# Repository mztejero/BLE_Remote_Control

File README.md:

This remote control is designed to send incremental inputs over Bluetooth Low Energy. In this specific application, steering and throttle values are set with the rotary encoders and the x and y values of the joysticks are set in a range of -100 to 100. All of these values are sent as a package over BLE.
Running the ```ble_test.py``` shows the unpacked messages being received as shown below. 

# ESP-IDF
The file architecture is split into each of the remote's functions with each ```.c``` file also havng a complementary ```.h``` file allowing variable and function sharng across the project.
The files can be found in ```BLE_Remote_Control/main```:
```
config.c
joystick.c
bluetooth.c
encoder.c
lcd.c
buttons.c
main.c
```
```config.c```      Sets up and names the GPIO's used on the ESP32. <br>
```joystick.c```    Reads ADC values from the joystick potentiometers, estimates offsets, and converts the values into a range from -100 to 100. <br>
```bluetooth.c```  Uses NimBLE to run the ESP32 as a server by advertising through a GAP and publishing data packets through a GATT at 50 Hz. <br>
```encoder.c```     Sets up interrupts on quadrature encoders A and B terminals with tasks for counting which are added to queues. <br>
```lcd.c ```        Handles communication with LCD 16x02 via I<sup>2</sup>C. Transfers data through 4-bit nibbles and prints values on the screen (as shown in first picture). <br>
```buttons.c```     Placeholder script for reading switch values from encoders and joysticks. These are not currently used in this project. <br>
```main.c```        Main script for initializing and running the project on ESP32.

# Schematics

This PCB is designed using the following components:

## SMD Components
ESP32-WROOM-32E -- Microcontroller used to run firmware, read sensors, write to actuators, and handle BLE communication. <br>
CP2102A USB-to-UART -- Interface for uploading code to the ESP32-WROOM-32E. The NPN transistors circuitry automatically put the ESP32 into bootloader mode when a new upload happens.<br>
<br>
PCF8574A I2C I/O for LCD communication -- Uses SCL and SDA to convert I<sup>2</sup>C data into bits to send to the LCD 16x02. Circuitry implements n-type MOSFETs for level shifting between 5V and 3V3 <br>
AMS1117-3.3 -- Converts 5V into 3.3V for components requiring 3V3<br>

## Hand-Soldered Components
Rotary Encoders -- Quadrature encoders with A and B terminals connected to GPIOs with pull-ups. Interrupts on these pull-ups are triggered upon rotation. <br>
Joysticks -- Use 2 potentiometers, one for x direction and one for y direction. These values are read through the ESP32's ADC. <br>
LCD 16x02 -- Displays characters on a 16×2 grid from data bits. <br>
Potentiometer -- Adjusts LCD lighting. <br>

# Final PCB Design

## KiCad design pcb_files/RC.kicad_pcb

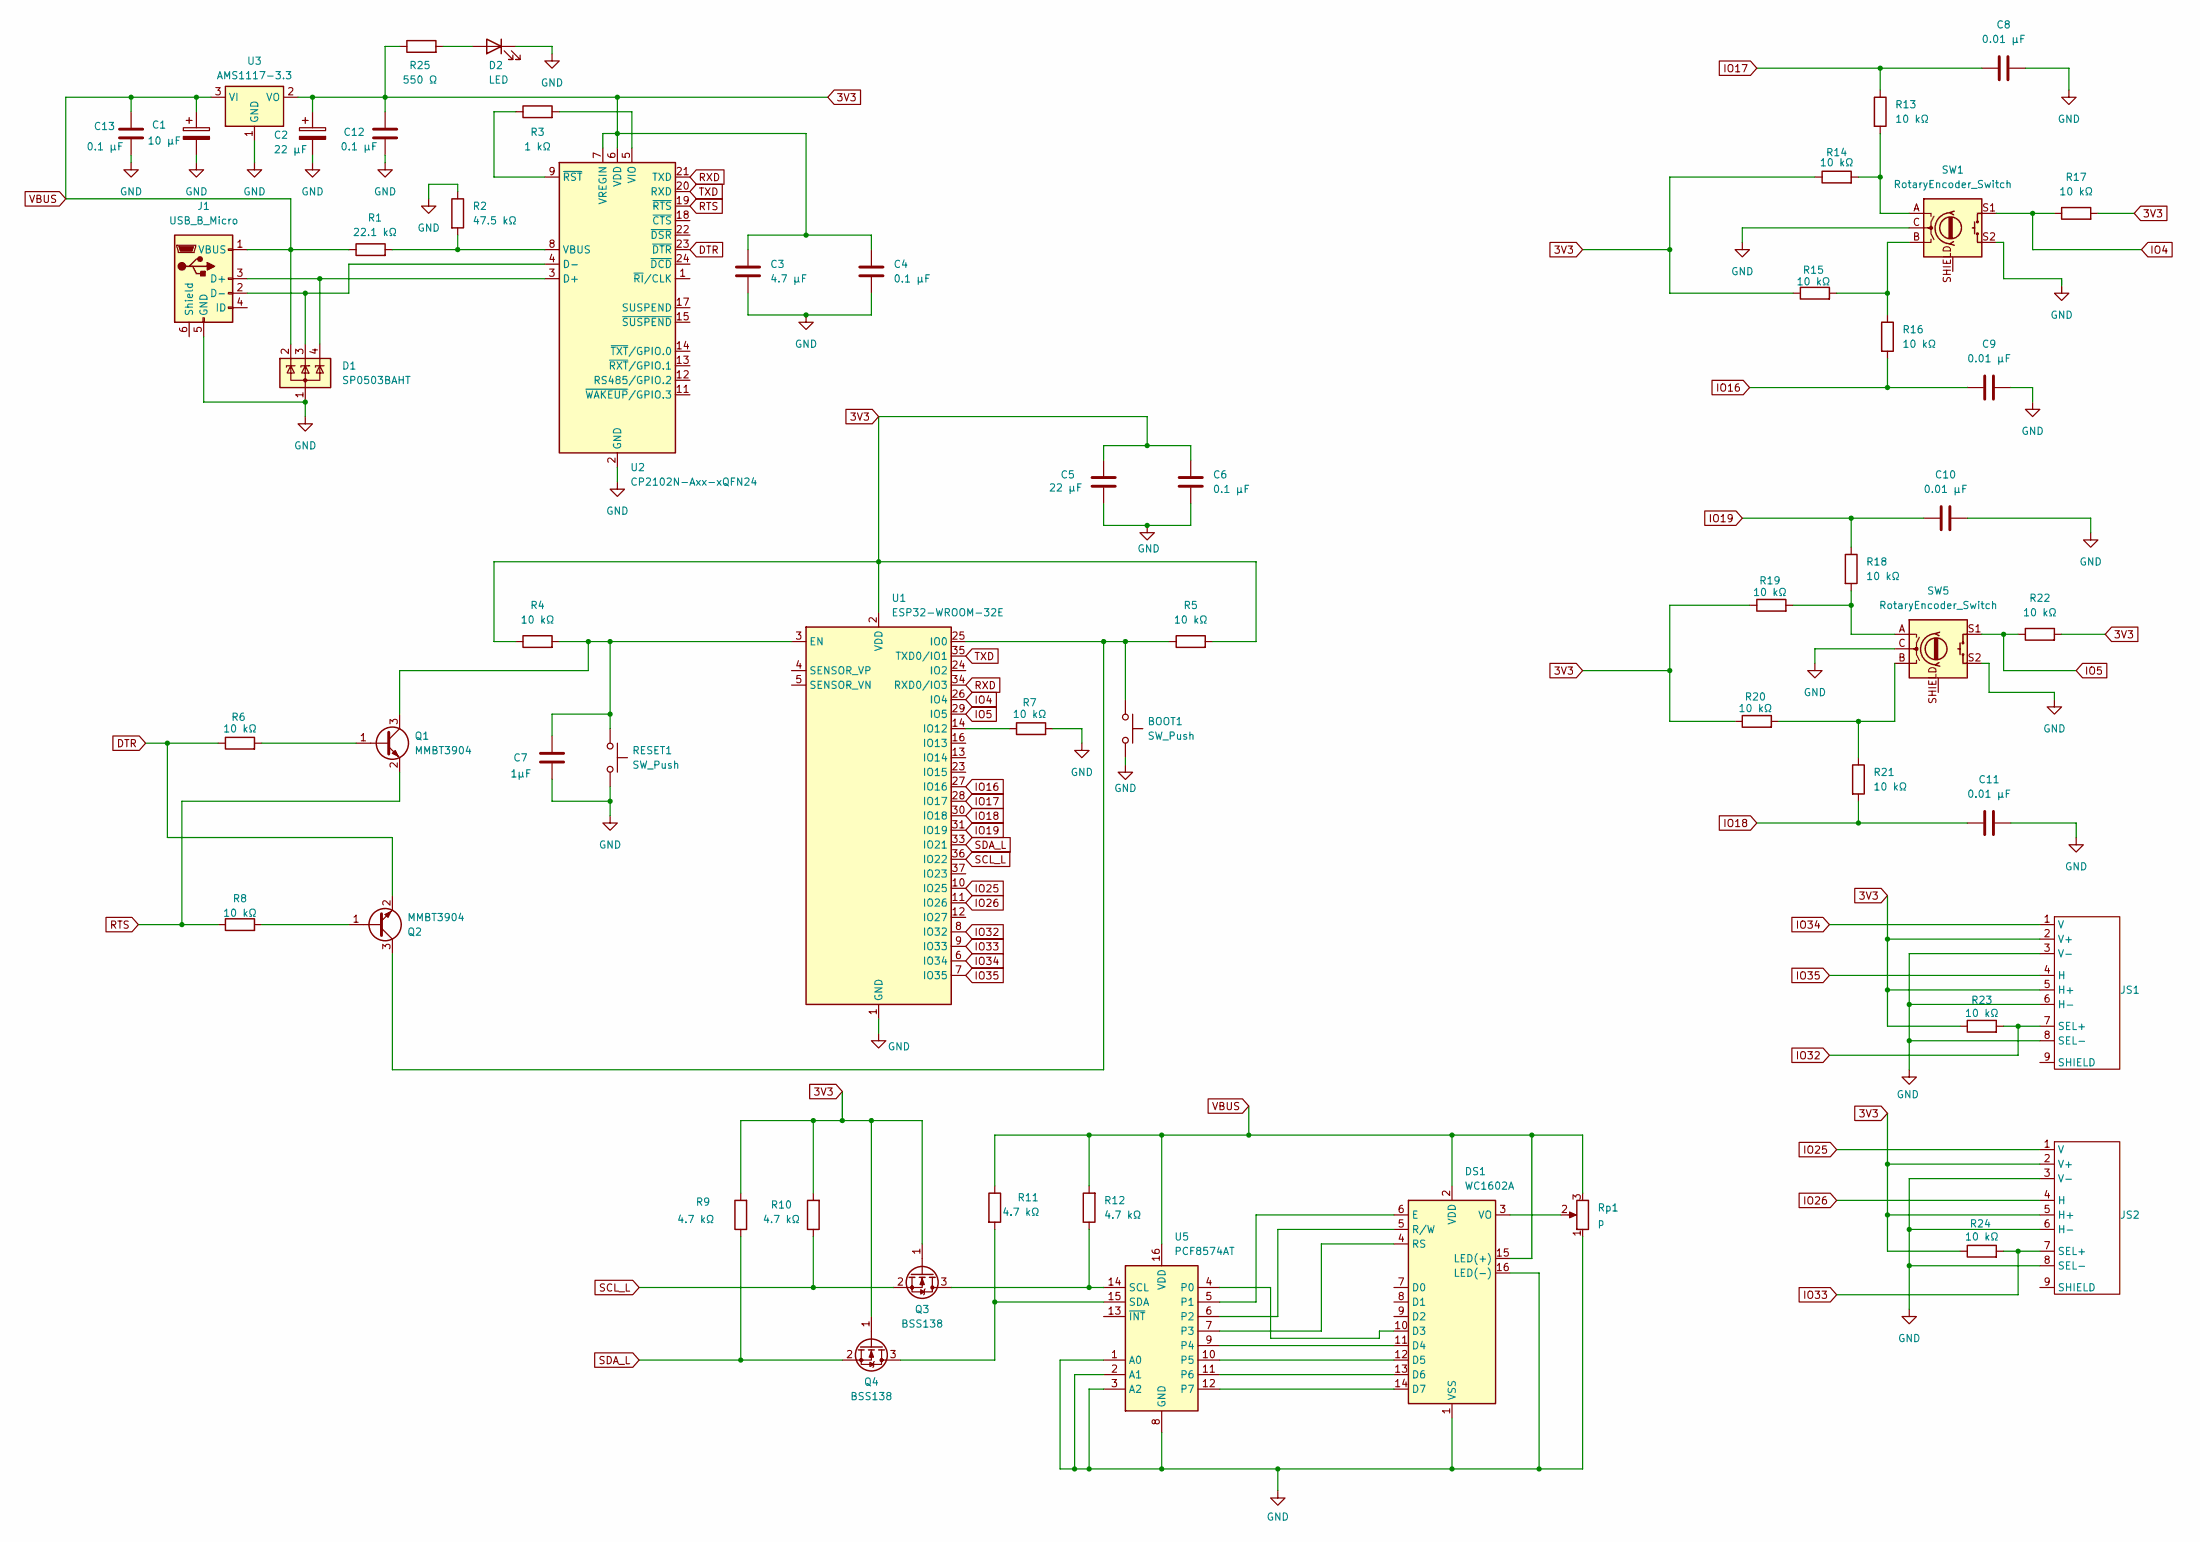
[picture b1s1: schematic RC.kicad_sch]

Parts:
BOOT1: SW_Push; SW_SPST_PTS647_Sx38
C1: 10 µF; CP_EIA-2012-12_Kemet-R
C2: 22 µF; CP_EIA-2012-12_Kemet-R
C3: 4.7 µF; C_0805_2012Metric
C4, C6, C12, C13: 0.1 µF; C_0603_1608Metric
C5: 22 µF; C_0805_2012Metric
C7: 1µF; C_0805_2012Metric
C8, C9, C10, C11: 0.01 µF; C_0603_1608Metric
D1: SP0503BAHT; SOT-143
D2: LED; LED_0603_1608Metric
DS1: WC1602A
J1: USB_B_Micro; USB_Micro-B_Amphenol_10103594-0001LF_Horizontal
JS1, JS2: Joystick
Q1, Q2: MMBT3904; SOT-23
Q3, Q4: BSS138; SOT-23
R1: 22.1 kΩ; R_0805_2012Metric
R2: 47.5 kΩ; R_0603_1608Metric
R3: 1 kΩ; R_0603_1608Metric
R4, R5, R6, R7, R8, R13, R14, R15, R16, R17, R18, R19, R20, R21, R22, R23, R24: 10 kΩ; R_0603_1608Metric
R9, R10, R11, R12: 4.7 kΩ; R_0603_1608Metric
R25: 550 Ω; R_0603_1608Metric
RESET1: SW_Push; SW_SPST_PTS647_Sx38
Rp1: p; Potentiometer_Bourns_3386P_Vertical
SW1, SW5: RotaryEncoder_Switch; Rotary_Encoder_RC
U1: ESP32-WROOM-32E
U2: CP2102N-Axx-xQFN24; QFN-24-1EP_4x4mm_P0.5mm_EP2.6x2.6mm
U3: AMS1117-3.3; SOT-223-3_TabPin2
U5: PCF8574AT; SOIC-16W_7.5x10.3mm_P1.27mm

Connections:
3V3: C2.1, C3.1, C4.1, C5.1, C6.1, C12.1, JS1.2 (V+), JS1.5 (H+), JS2.2 (V+), JS2.5 (H+), Q3.1 (G), Q4.1 (G), R4.1, R5.2, R9.2, R10.2, R14.1, R15.1, R17.2, R19.1, R20.1, R22.2, R23.1, R24.1, R25.1, U1.2 (VDD), U2.6 (VDD), U2.7 (VREGIN), U3.2 (VO)
DTR: Q2.2 (E), R6.1, U2.23 (~DTR)
GND: BOOT1.2, C1.2, C2.2, C3.2, C4.2, C5.2, C6.2, C7.2, C8.2, C9.2, C10.2, C11.2, C12.2, C13.2, D1.1 (A), D2.1 (K), DS1.1 (VSS), DS1.16 (LED(-)), J1.5 (GND), JS1.3 (V-), JS1.6 (H-), JS1.8 (SEL-), JS2.3 (V-), JS2.6 (H-), JS2.8 (SEL-), R2.1, R7.2, RESET1.2, Rp1.1, SW1.C, SW1.S2, SW5.C, SW5.S2, U1.1 (GND), U1.15 (GND), U1.38 (GND), U1.39 (GND), U2.2 (GND), U2.25 (GND), U3.1 (GND), U5.1 (A0), U5.2 (A1), U5.3 (A2), U5.8 (GND)
IO4: R17.1, SW1.S1, U1.26 (IO4)
IO5: R22.1, SW5.S1, U1.29 (IO5)
IO16: C9.1, R16.2, U1.27 (IO16)
IO17: C8.1, R13.1, U1.28 (IO17)
IO18: C11.1, R21.2, U1.30 (IO18)
IO19: C10.1, R18.1, U1.31 (IO19)
IO25: JS2.1 (V), U1.10 (IO25)
IO26: JS2.4 (H), U1.11 (IO26)
IO32: JS1.7 (SEL+), R23.2, U1.8 (IO32)
IO33: JS2.7 (SEL+), R24.2, U1.9 (IO33)
IO34: JS1.1 (V), U1.6 (IO34)
IO35: JS1.4 (H), U1.7 (IO35)
unnamed: D2.2 (A), R25.2
unnamed: DS1.10 (D3), U5.4 (P0)
unnamed: DS1.11 (D4), U5.9 (P4)
unnamed: DS1.12 (D5), U5.10 (P5)
unnamed: DS1.13 (D6), U5.11 (P6)
unnamed: DS1.14 (D7), U5.12 (P7)
unnamed: DS1.6 (E), U5.5 (P1)
unnamed: DS1.4 (RS), U5.7 (P3)
unnamed: DS1.5 (R/W), U5.6 (P2)
unnamed: DS1.3 (VO), Rp1.2
unnamed: D1.4 (K), J1.3 (D+), U2.3 (D+)
unnamed: D1.3 (K), J1.2 (D-), U2.4 (D-)
unnamed: Q1.1 (B), R6.2
unnamed: C7.1, Q1.3 (C), R4.2, RESET1.1, U1.3 (EN)
unnamed: Q2.1 (B), R8.2
unnamed: BOOT1.1, Q2.3 (C), R5.1, U1.25 (IO0)
unnamed: Q3.3 (D), R12.1, U5.14 (SCL)
unnamed: Q4.3 (D), R11.2, U5.15 (SDA)
unnamed: R13.2, R14.2, SW1.A
unnamed: R15.2, R16.1, SW1.B
unnamed: R18.2, R19.2, SW5.A
unnamed: R20.2, R21.1, SW5.B
unnamed: R7.1, U1.14 (IO12)
unnamed: R1.2, R2.2, U2.8 (VBUS)
unnamed: R3.2, U2.5 (VIO)
unnamed: R3.1, U2.9 (~RST)
RTS: Q1.2 (E), R8.1, U2.19 (~RTS)
RXD: U1.34 (RXD0/IO3), U2.21 (TXD)
SCL_L: Q3.2 (S), R10.1, U1.36 (IO22)
SDA_L: Q4.2 (S), R9.1, U1.33 (IO21)
TXD: U1.35 (TXD0/IO1), U2.20 (RXD)
VBUS: C1.1, C13.1, D1.2 (K), DS1.2 (VDD), DS1.15 (LED(+)), J1.1 (VBUS), R1.1, R11.1, R12.2, Rp1.3, U3.3 (VI), U5.16 (VDD)

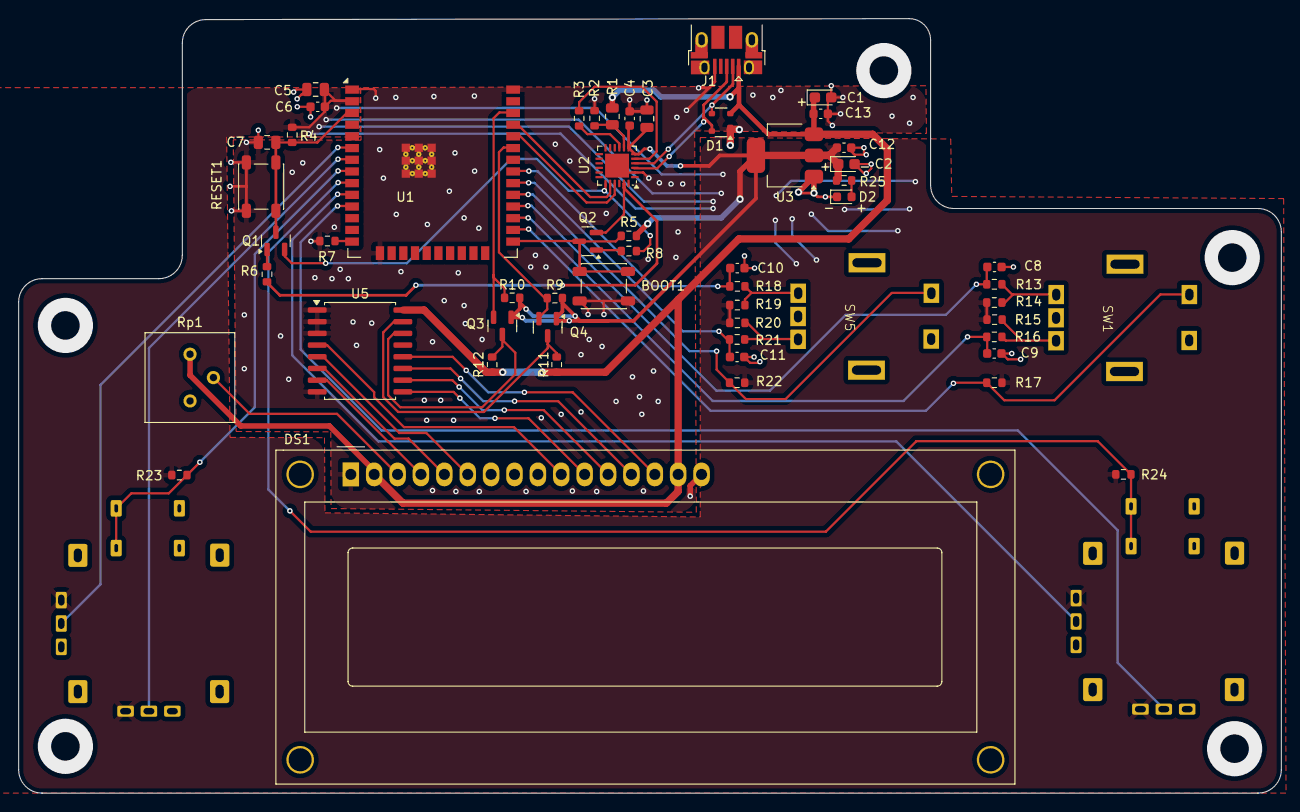
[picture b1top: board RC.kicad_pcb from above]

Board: 2 copper layers, 137.2 x 84.1 mm, 57 parts (0 on the bottom side), 47 nets.

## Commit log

2025-09-12 file replacement
2025-09-12 ble output
2025-09-13 gitignore
2025-09-13 Remove .DS_Store and add to .gitignore
2025-09-13 remove DS_Store
